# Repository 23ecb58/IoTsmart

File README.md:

View this project on [CADLAB.io](https://cadlab.io/project/29224). 

# IoTsmart

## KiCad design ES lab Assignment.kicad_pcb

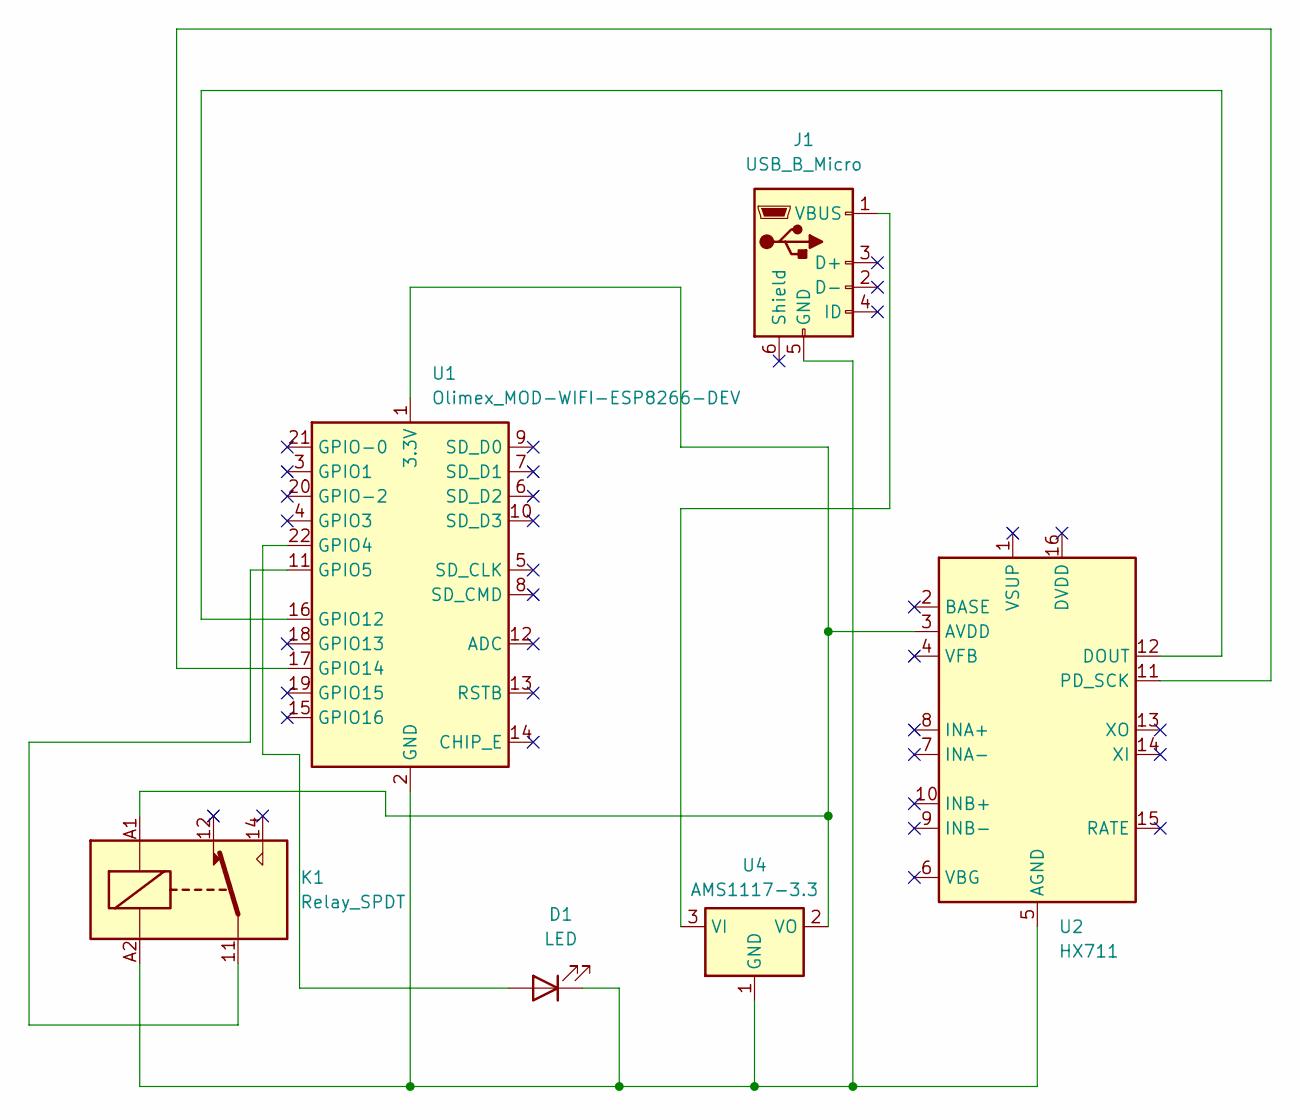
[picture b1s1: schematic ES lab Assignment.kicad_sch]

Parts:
D1: LED; LED_D1.8mm_W1.8mm_H2.4mm_Horizontal_O1.27mm_Z1.6mm
J1: USB_B_Micro; USB_Micro-B_Amphenol_10103594-0001LF_Horizontal
K1: Relay_SPDT; Relay_SPDT_Finder_32.21-x000
U1: Olimex_MOD-WIFI-ESP8266-DEV
U2: HX711; SOP-16_3.9x9.9mm_P1.27mm
U4: AMS1117-3.3; SOT-223-3_TabPin2

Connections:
unnamed: D1.2 (A), U1.22 (GPIO4)
unnamed: D1.1 (K), J1.5 (GND), K1.A2, U1.2 (GND), U2.5 (AGND), U4.1 (GND)
unnamed: J1.1 (VBUS), U4.3 (VI)
unnamed: K1.A1, U1.1 (3.3V), U2.3 (AVDD), U4.2 (VO)
unnamed: K1.11, U1.11 (GPIO5)
unnamed: U1.16 (GPIO12), U2.12 (DOUT)
unnamed: U1.17 (GPIO14), U2.11 (PD_SCK)

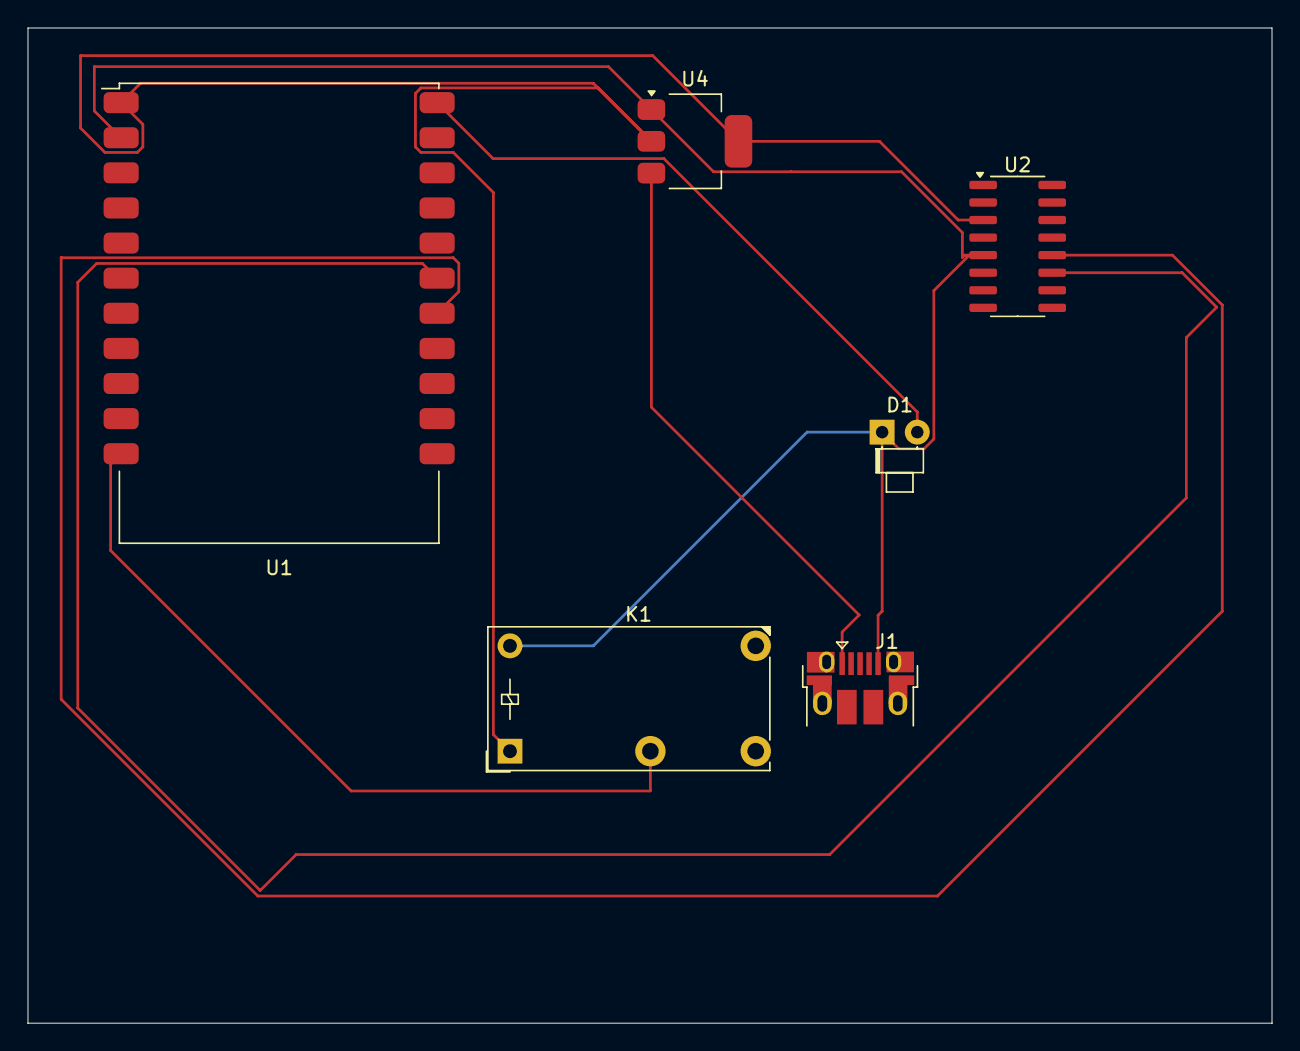
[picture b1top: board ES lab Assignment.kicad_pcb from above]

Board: 2 copper layers, 90.0 x 72.0 mm, 6 parts (0 on the bottom side), 7 nets.

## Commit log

2025-04-09 pcb assignment
2025-04-09 Backlink to CADLAB.io has been added.
